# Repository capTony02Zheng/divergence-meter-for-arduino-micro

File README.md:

# divergence-meter-for-arduino-micro
 This is a project use for creating an divergence meter. Thank you for visiting.
-----------------------------------------------------------------------

 Code are well written but need the user to update the IRdata to match the 1838IR remote control. Also the ds3231 module need to be updated with
other code, which is not provided here.

 The PCB is developed with kiCAD.

 To start up from nothing, here's the few steps you need to follow:
-----------------------------------------------------------------------
 Get all the component you need, which includes:

// An arduino micro board;
// A pcb that is printed with the file provided; (this pcb is 51mm * 130mm in size)
// A ds3231 time module;
// An IR1838 module with corresponding remote control;
// One or two 5v to 170v boost module;
// multiple resistors of 10k and 100k;
// four hv5523pg-g chips; you can buy some here: https://www.microchip.com/en-us/product/hv5522#document-table;

After gathering all the component, it is time for you to do the soldering work. It is recommended to solder the 4 chips first, then the arduino board.

About the boost module:
pin "170vin1" and "170vin2" should be connected to the 170v output from the boost module. pin "5VFB" shoule be connected to the 5v input on the boost module.

About external power source(Optional):
if you decided to use other battery module to support the arduino, the pins "BatteryIn" and "BatteryGround" is provided, the supporting volts should not exceeds the the range that arduino micro can accept.

About the resistors:
It is recommended to connect 10k or 20k resistors at the pins "170V" and "170V2";
for places like "t1dp" and "t2dp", a 100k resistor is recommended.

About the pins:
you can directly connected the nixie tubes pins to the correponding hole in the pcb, like the t1n1 means tube1 number1, at displays it is the number "1" of the left most nixie tube. or you can use ph2.0 sockets with 12 pins.

Features and controls of the divergence meter:
-----------------------------------------------------------------------
There are 6 mode for the divergence meter, the first one displays current time; the second one displays current date; the third one
displays Celsius temperature recorded by ds3231; the fourth mode displays displays worldline; the fifth mode displays the number you entered;
the sixth one diplays number from 0 to 9 to protect the tubes;

//About the control:

Power: close or open;

Menu: First time you pressed you entered menu mode, then you can push button from 0 to 5 to choose corresponding mode, which will help you leave the menu mode automatically. Or at menu mode you can use arrow to go to the next or previous mode, then press menu again to exit the menu mode;

Play: At worldline mode you can use it to get in and out of random display mode; At manual input mode you can use it to open or close displays.

"-": as decimal point in manual input mode.

"C": At manual input mode you can use it to change wether the decimal point and number are display in one tube or not, which can save some spaces. At worldline mode you can change the number to be displayed one by one or all by instant.

"return": clear all the input data at the manual display mode.

left and right arrow: when at worldline mode and the menu mode is off, you can use it to display the next or previous worldline.

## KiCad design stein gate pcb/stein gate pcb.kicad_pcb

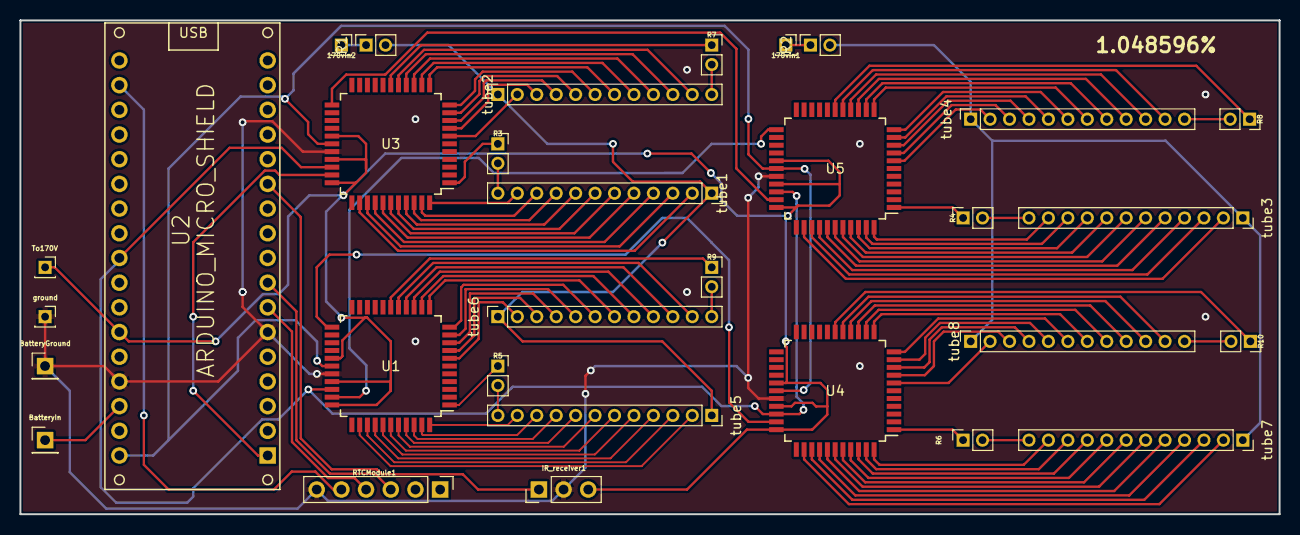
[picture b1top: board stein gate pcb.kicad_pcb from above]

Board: 2 copper layers, 129.5 x 50.8 mm, 31 parts (0 on the bottom side), 113 nets.

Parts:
170vin1, 170vin2: Conn_01x01_Female; PinSocket_1x01_P2.00mm_Vertical
BatteryGround: Conn_01x01_Female; PinHeader_1x01_P2.54mm_Vertical
BatteryIn: Conn_01x01_Female; PinHeader_1x01_P2.54mm_Vertical
IR_receiver1: Conn_01x03_Female; PinHeader_1x03_P2.54mm_Vertical
R1, R2, R3, R4, R5, R6, R7, R8, R9, R10: R; PinSocket_1x02_P2.00mm_Vertical
RTCModule1: Conn_01x06_Female; PinHeader_1x06_P2.54mm_Vertical
To170V: Conn_01x01_Female; PinSocket_1x01_P2.00mm_Vertical
U1, U3, U4, U5: hv5522(first_created); PQFP-44_10x10mm_P0.8mm
U2: ARDUINO_MICRO_SHIELD
ground: Conn_01x01_Female; PinSocket_1x01_P2.00mm_Vertical
tube1, tube2, tube3, tube4, tube5, tube6, tube7, tube8: ph2.0_terminal_for_5440; PinSocket_1x12_P2.00mm_Vertical

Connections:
/3.3VFB: RTCModule1.5, U2.3.3V
/5VFB: IR_receiver1.3, To170V.1, U1.27 (POL), U1.30 (VDD), U1.33 (BL), U2.5V (+5V), U3.27 (POL), U3.30 (VDD), U3.33 (BL), U4.27 (POL), U4.30 (VDD), U4.33 (BL), U5.27 (POL), U5.30 (VDD), U5.33 (BL)
/170V: R2.2, tube3.1, tube4.1, tube7.1, tube8.1
/170V2: R1.2, tube1.1, tube2.1, tube5.1, tube6.1
/Clock: U1.28 (CLK), U2.SCK, U3.28 (CLK), U4.28 (CLK), U5.28 (CLK)
/DataFromBoard: U2.MO (MOSI), U3.32 (Data_in)
/IRdata: IR_receiver1.1, U2.7
/SCL: RTCModule1.3, U2.3 (3(PWM)/SCL)
/SDA: RTCModule1.4, U2.2 (2/SDA)
/dataout1: U3.23 (Data_out), U5.32 (Data_in)
/dataout2: U1.32 (Data_in), U5.23 (Data_out)
/dataout3: U1.23 (Data_out), U4.32 (Data_in)
/latch: U1.31 (Latch_), U2.A5, U3.31 (Latch_), U4.31 (Latch_), U5.31 (Latch_)
/t1dp: R3.1, U3.1 (HVOUT_11)
/t1n0: U3.44 (HVOUT_10), tube1.11
/t1n1: U3.35 (HVOUT_1), tube1.2
/t1n2: U3.36 (HVOUT_2), tube1.3
/t1n3: U3.37 (HVOUT_3), tube1.4
/t1n4: U3.38 (HVOUT_4), tube1.5
/t1n5: U3.39 (HVOUT_5), tube1.6
/t1n6: U3.40 (HVOUT_6), tube1.7
/t1n7: U3.41 (HVOUT_7), tube1.8
/t1n8: U3.42 (HVOUT_8), tube1.9
/t1n9: U3.43 (HVOUT_9), tube1.10
/t2dp: R7.1, U3.17 (HVOUT_27)
/t2n0: U3.16 (HVOUT_26), tube2.11
/t2n1: U3.7 (HVOUT_17), tube2.2
/t2n2: U3.8 (HVOUT_18), tube2.3
/t2n3: U3.9 (HVOUT_19), tube2.4
/t2n4: U3.10 (HVOUT_20), tube2.5
/t2n5: U3.11 (HVOUT_21), tube2.6
/t2n6: U3.12 (HVOUT_22), tube2.7
/t2n7: U3.13 (HVOUT_23), tube2.8
/t2n8: U3.14 (HVOUT_24), tube2.9
/t2n9: U3.15 (HVOUT_25), tube2.10
/t3dp: R4.1, U5.1 (HVOUT_11)
/t3n0: U5.44 (HVOUT_10), tube3.11
/t3n1: U5.35 (HVOUT_1), tube3.2
/t3n2: U5.36 (HVOUT_2), tube3.3
/t3n3: U5.37 (HVOUT_3), tube3.4
/t3n4: U5.38 (HVOUT_4), tube3.5
/t3n5: U5.39 (HVOUT_5), tube3.6
/t3n6: U5.40 (HVOUT_6), tube3.7
/t3n7: U5.41 (HVOUT_7), tube3.8
/t3n8: U5.42 (HVOUT_8), tube3.9
/t3n9: U5.43 (HVOUT_9), tube3.10
/t4dp: R8.1, U5.17 (HVOUT_27)
/t4n0: U5.16 (HVOUT_26), tube4.11
/t4n1: U5.7 (HVOUT_17), tube4.2
/t4n2: U5.8 (HVOUT_18), tube4.3
/t4n3: U5.9 (HVOUT_19), tube4.4
/t4n4: U5.10 (HVOUT_20), tube4.5
/t4n5: U5.11 (HVOUT_21), tube4.6
/t4n6: U5.12 (HVOUT_22), tube4.7
/t4n7: U5.13 (HVOUT_23), tube4.8
/t4n8: U5.14 (HVOUT_24), tube4.9
/t4n9: U5.15 (HVOUT_25), tube4.10
/t5dp: R5.1, U1.1 (HVOUT_11)
/t5n0: U1.44 (HVOUT_10), tube5.11
/t5n1: U1.35 (HVOUT_1), tube5.2
/t5n2: U1.36 (HVOUT_2), tube5.3
/t5n3: U1.37 (HVOUT_3), tube5.4
/t5n4: U1.38 (HVOUT_4), tube5.5
/t5n5: U1.39 (HVOUT_5), tube5.6
/t5n6: U1.40 (HVOUT_6), tube5.7
/t5n7: U1.41 (HVOUT_7), tube5.8
/t5n8: U1.42 (HVOUT_8), tube5.9
/t5n9: U1.43 (HVOUT_9), tube5.10
/t6dp: R9.1, U1.17 (HVOUT_27)
/t6n0: U1.16 (HVOUT_26), tube6.11
/t6n1: U1.7 (HVOUT_17), tube6.2
/t6n2: U1.8 (HVOUT_18), tube6.3
/t6n3: U1.9 (HVOUT_19), tube6.4
/t6n4: U1.10 (HVOUT_20), tube6.5
/t6n5: U1.11 (HVOUT_21), tube6.6
/t6n6: U1.12 (HVOUT_22), tube6.7
/t6n7: U1.13 (HVOUT_23), tube6.8
/t6n8: U1.14 (HVOUT_24), tube6.9
/t6n9: U1.15 (HVOUT_25), tube6.10
/t7dp: R6.1, U4.1 (HVOUT_11)
/t7n0: U4.44 (HVOUT_10), tube7.11
/t7n1: U4.35 (HVOUT_1), tube7.2
/t7n2: U4.36 (HVOUT_2), tube7.3
/t7n3: U4.37 (HVOUT_3), tube7.4
/t7n4: U4.38 (HVOUT_4), tube7.5
/t7n5: U4.39 (HVOUT_5), tube7.6
/t7n6: U4.40 (HVOUT_6), tube7.7
/t7n7: U4.41 (HVOUT_7), tube7.8
/t7n8: U4.42 (HVOUT_8), tube7.9
/t7n9: U4.43 (HVOUT_9), tube7.10
/t8dp: R10.1, U4.17 (HVOUT_27)
/t8n0: U4.16 (HVOUT_26), tube8.11
/t8n1: U4.7 (HVOUT_17), tube8.2
/t8n2: U4.8 (HVOUT_18), tube8.3
/t8n3: U4.9 (HVOUT_19), tube8.4
/t8n4: U4.10 (HVOUT_20), tube8.5
/t8n5: U4.11 (HVOUT_21), tube8.6
/t8n6: U4.12 (HVOUT_22), tube8.7
/t8n7: U4.13 (HVOUT_23), tube8.8
/t8n8: U4.14 (HVOUT_24), tube8.9
/t8n9: U4.15 (HVOUT_25), tube8.10
GND: BatteryGround.1, IR_receiver1.2, RTCModule1.6, U1.29 (VSS(GND)), U2.GND, U3.29 (VSS(GND)), U4.29 (VSS(GND)), U5.29 (VSS(GND)), ground.1
unnamed: 170vin1.1, R2.1
unnamed: 170vin2.1, R1.1
unnamed: BatteryIn.1, U2.VI (VIN)
unnamed: R3.2, tube1.12
unnamed: R7.2, tube2.12
unnamed: R4.2, tube3.12
unnamed: R8.2, tube4.12
unnamed: R5.2, tube5.12
unnamed: R9.2, tube6.12
unnamed: R6.2, tube7.12
unnamed: R10.2, tube8.12
